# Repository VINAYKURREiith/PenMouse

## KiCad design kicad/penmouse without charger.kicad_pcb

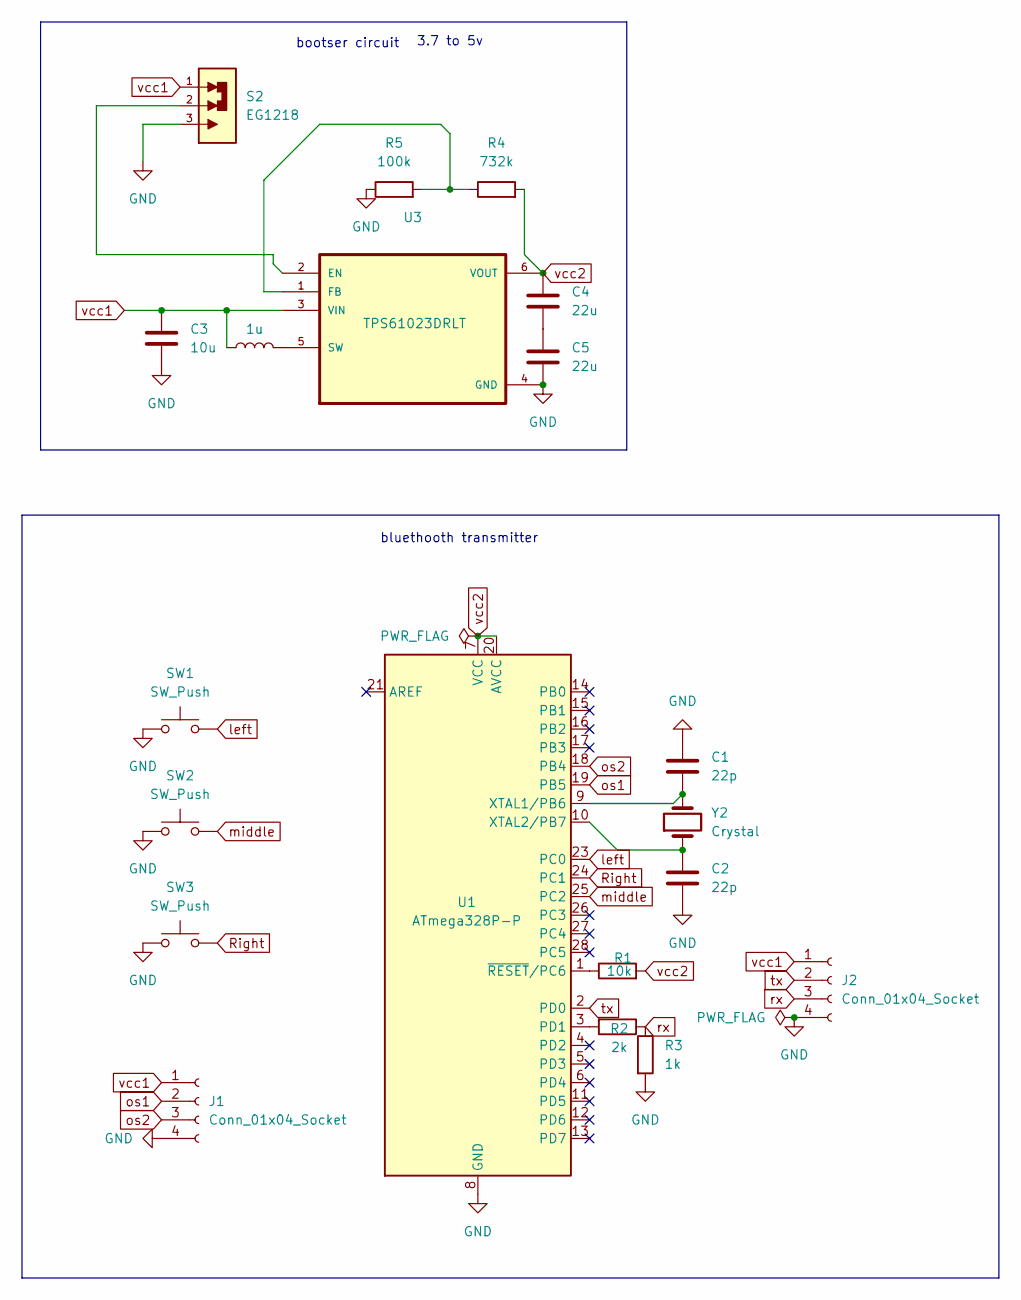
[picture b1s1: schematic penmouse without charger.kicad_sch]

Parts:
C1, C2: 22p; C_0402_1005Metric
C3: 10u; C_0402_1005Metric
C4, C5: 22u; C_0402_1005Metric
J1, J2: Conn_01x04_Socket; JST_EH_B4B-EH-A_1x04_P2.50mm_Vertical
L3: 1u; L_0402_1005Metric
R1: 10k; R_0402_1005Metric
R2: 2k; R_0402_1005Metric
R3: 1k; R_0402_1005Metric
R4: 732k; R_0402_1005Metric
R5: 100k; R_0402_1005Metric
S2: EG1218; SW_EG1218
SW1, SW2, SW3: SW_Push; SW_PUSH_1P1T_6x3.5mm_H4.3_APEM_MJTP1243
U1: ATmega328P-P; DIP-28_W7.62mm
U3: TPS61023DRLT; SOT50P160X60-6N
Y2: Crystal; Crystal_HC52-8mm_Vertical

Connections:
GND: C1.1, C2.2, C3.1, C5.2, J1.4, J2.4, R3.2, R5.1, S2.3, SW1.1, SW2.1, SW3.1, U1.8 (GND), U1.22 (GND), U3.4 (GND)
unnamed: C4.2, C5.1
unnamed: R2.2, U1.3 (PD1)
unnamed: C1.2, U1.9 (XTAL1/PB6), Y2.2
unnamed: C2.1, U1.10 (XTAL2/PB7), Y2.1
unnamed: R1.1, U1.1 (~RESET/PC6)
unnamed: S2.2, U3.2 (EN)
unnamed: R4.1, R5.2, U3.1 (FB)
unnamed: L3.2, U3.5 (SW)
Right: SW3.2, U1.24 (PC1)
left: SW1.2, U1.23 (PC0)
middle: SW2.2, U1.25 (PC2)
os1: J1.2, U1.19 (PB5)
os2: J1.3, U1.18 (PB4)
rx: J2.3, R2.1, R3.1
tx: J2.2, U1.2 (PD0)
vcc1: C3.2, J1.1, J2.1, L3.1, S2.1, U3.3 (VIN)
vcc2: C4.1, R1.2, R4.2, U1.7 (VCC), U1.20 (AVCC), U3.6 (VOUT)

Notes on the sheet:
bootser circuit
bluethooth transmitter
3.7 to 5v

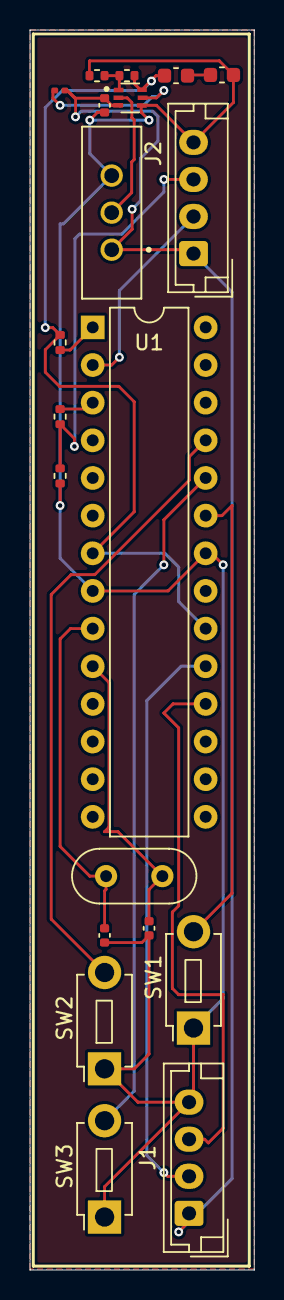
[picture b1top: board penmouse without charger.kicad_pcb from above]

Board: 2 copper layers, 15.1 x 83.6 mm, 20 parts (0 on the bottom side), 18 nets.

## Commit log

2025-03-09 kicad files
2025-03-09 empty file
2025-03-09 bom file added
2025-03-09 gbr files
2025-03-09 Create xx
2025-03-09 files
2025-03-09 emptyfile
